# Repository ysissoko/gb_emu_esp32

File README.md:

# GB ESP32 Emulator

A Game Boy (DMG) and Game Boy Color (CGB) emulator running on the **ESP32-S3** microcontroller, built with ESP-IDF and FreeRTOS. The project includes a custom PCB design and achieves ~59.7 FPS with cycle-accurate emulation on embedded hardware.

---

## Features

### Emulation Core
- **Cycle-accurate SM83 CPU** — full base instruction set + CB-prefixed opcodes, correct flag behavior, HALT bug
- **Interrupt system** — VBLANK, STAT, TIMER, SERIAL, JOYPAD with proper IME/EI delay semantics
- **DMA** — OAM DMA (640 T-cycles), General DMA, and HDMA (HBlank-triggered 16-byte blocks)
- **Timer** — DIV, TIMA/TMA/TAC with falling-edge detection and 4-M-cycle overflow delay
- **Scanline PPU** — background, window, and sprite (up to 10/scanline) layers; STAT interrupts edge-triggered on LY/LYC comparison
- **Boot ROM** — 256-byte DMG boot ROM execution

### Game Boy Color (CGB)
- Mode detection via cartridge header byte `0x0143`
- VRAM banking (`VBK` 0xFF4F) — 2 × 8 KB banks in PSRAM
- WRAM banking (`SVBK` 0xFF70) — banks 2–7 in PSRAM
- CGB palette RAM — 8 BG + 8 OBJ palettes via `BGPI/BGPD`, `OBPI/OBPD`
- Tile attributes from VRAM bank 1 (palette index, H/V flip, VRAM bank select, BG-to-OBJ priority)
- 15-bit RGB color with GBC color correction (Gambatte-style formula)
- Double-speed CPU mode (`KEY1` 0xFF4D) — 2× CPU cycles, PPU/timer at 1×

### Cartridge Support (MBC)
| MBC | ROM Banks | RAM Banks | Notes |
|-----|-----------|-----------|-------|
| MBC1 | 32 | 4 | 512 KB ROM / 32 KB RAM |
| MBC2 | 16 | — | 512 × 4-bit internal RAM |
| MBC3 | 128 | 4 | + Real-Time Clock (RTC) |
| MBC5 | 512 | 16 | Most GBC games |

Extended ROM banks (>32 KB) are stored in PSRAM.

### Display
- **ST7789V** 240×240 SPI LCD at 80 MHz
- Game Boy 160×144 output upscaled to 240×240 (1.5×, centered)
- RGB565 framebuffer → BGR565 conversion for panel wiring
- Chunked DMA transfers (48-line chunks, 3 transfers per frame)
- Asynchronous rendering task — display I/O never blocks the emulation loop

### Storage & Saves
- SD card (FAT32, SPI-shared bus) for ROMs and save files
- `.sav` files for battery-backed SRAM, auto-saved every ~16 frames
- RTC persistence across sessions (MBC3)
- Async save task pinned to Core 0

### Input
- 8 tactile buttons — A, B, SELECT, START, UP, DOWN, LEFT, RIGHT
- Active-LOW GPIO with internal pull-ups and 20 ms debounce
- Joypad interrupt on key press

### Menu
- ROM browser with scrollable list (up to 64 entries)
- Text rendering on LCD, joypad navigation
- Menu framebuffer (~150 KB) freed before ROM loading

---

## Architecture

```
┌──────────────────────────────────────────────────────────────────┐
│                         Emulator                                 │
│              State machine: MENU ↔ RUNNING_GAME                  │
│         Task scheduling, ROM loading, component wiring           │
└───────────────────┬──────────────────────────────────────────────┘
                    │
       ┌────────────┼────────────┐
       │            │            │
┌──────▼──────┐ ┌───▼──────┐ ┌──▼──────────┐
│    CPU      │ │   PPU    │ │  MemoryBus  │
│  (SM83)     │ │ Scanline │ │   (MMU)     │
│  Executes   │ │ renderer │ │  Banking    │
│  instrs     │ │ 456 cy/  │ │  I/O mux   │
│  ~60 FPS    │ │ scanline │ │  MBC 1/3/5 │
└──────┬──────┘ └───┬──────┘ └──┬──────────┘
       │            │            │
       └────────────┼────────────┘
                    │
     ┌──────────────┼──────────────────┐
     │              │                  │
┌────▼───┐    ┌─────▼────┐    ┌───────▼────┐
│ Timer  │    │  Joypad  │    │  APU/Ser.  │
│DIV/TIMA│    │8 buttons │    │  (stub)    │
└────────┘    └──────────┘    └────────────┘

Display pipeline:
PPU framebuffer ──► Async render task ──► ST7789V (DMA, 3 chunks)

Storage:
SD card (FAT32) ──► ROM loading / .sav files ──► async save task
```

### Component Breakdown

| Component | File | Responsibility |
|-----------|------|----------------|
| Emulator | `emulator.cpp` | App states, task creation, ROM lifecycle |
| CPU | `cpu.cpp` (1 654 lines) | SM83 instruction execution, interrupts, DMA |
| PPU | `ppu.cpp` (754 lines) | Scanline rendering, STAT, VBLANK, CGB palettes |
| MemoryBus | `memory_bus.cpp` (1 143 lines) | Address decoding, MBC, PSRAM banking, I/O registers |
| Timer | `timer.cpp` | DIV/TIMA/TMA/TAC, overflow delay |
| Joypad | `joypad.hpp` | GPIO debounce, P14/P15 multiplexed reads |
| LCD Display | `lcd_display.cpp` | ST7789V SPI + DMA, RGB565 output |
| Storage | `storage.cpp` | SD card, FAT32, ROM enumeration |
| Save Manager | `save_manager.cpp` | SRAM persistence, async write to `.sav` |
| Menu | `menu.cpp` | ROM browser UI, framebuffer rendering |
| APU | `apu.cpp` | Stub — register map only |
| Serial | `serial.cpp` | Stub — SB/SC, debug accumulation |

---

## Memory Map

| Address | Region |
|---------|--------|
| `0x0000–0x00FF` | Boot ROM (DMG, 256 B; disabled after boot) |
| `0x0000–0x3FFF` | ROM Bank 0 (fixed) |
| `0x4000–0x7FFF` | ROM Bank N (MBC-switched, in PSRAM) |
| `0x8000–0x9FFF` | VRAM (8 KB; bank 0/1 in CGB via PSRAM) |
| `0xA000–0xBFFF` | External RAM (MBC; up to 32 KB in PSRAM) |
| `0xC000–0xCFFF` | WRAM Bank 0 |
| `0xD000–0xDFFF` | WRAM Bank 1 (banks 2–7 in CGB via PSRAM) |
| `0xE000–0xFDFF` | Echo RAM (mirrors 0xC000–0xDDFF) |
| `0xFE00–0xFE9F` | OAM (160 B, sprite attributes) |
| `0xFF00–0xFF7F` | I/O Registers |
| `0xFF80–0xFFFE` | HRAM (127 B) |
| `0xFFFF` | IE register |

---

## Hardware

### Microcontroller — ESP32-S3-WROOM-1
- Dual-core Xtensa LX7 at 240 MHz
- 512 KB internal SRAM + 8 MB PSRAM (extended ROM/RAM banks, CGB extras)
- 16 MB Flash

### Pin Mapping

| Function | GPIO |
|----------|------|
| **Joypad** | |
| A | 5 |
| B | 6 |
| UP | 15 |
| DOWN | 16 |
| RIGHT | 17 |
| LEFT | 18 |
| START | 21 |
| SELECT | 47 |
| **SPI Bus (shared)** | |
| MOSI | 11 |
| MISO | 13 |
| SCK | 12 |
| **ST7789V LCD** | |
| CS | 10 |
| RST | 8 |
| DC | 9 |
| Backlight | 7 |
| **SD Card** | |
| CS | 4 |
| **Battery ADC** | 38 |
| **Status LEDs** | 41, 42 |
| **USB** | 19 (D−), 20 (D+) |

### PCB
A custom KiCad board design is included in `main_board/` with JLCPCB production files. The board integrates the ESP32-S3, ST7789V LCD connector, SD slot, LiPo charging circuit, 8 tactile buttons, RGB LED, and USB-C port.

---

## Performance Optimizations

- **IRAM placement** (`IRAM_ATTR`) on all hot-path functions (CPU execute, PPU step, memory read/write) — avoids flash cache misses on the Xtensa core
- **Branch prediction hints** (`LIKELY` / `UNLIKELY` macros) throughout instruction dispatch
- **Async PPU rendering** — PPU queues completed framebuffers; a dedicated FreeRTOS task drives the LCD, so display I/O never stalls the emulation loop
- **Chunked DMA** — 48-line (23 KB) buffers sent in 3 transfers; DMA completion semaphore prevents tearing
- **Frame skipping** — dynamically skips PPU rendering when the CPU falls behind
- **Compiler flags** — `-O3 -ffast-math -funroll-loops` (see `CMakeLists.txt` / `optimize.sh`)
- **ScanlineContext** struct — caches frequently-read PPU registers for each scanline to avoid repeated MMU calls

---

## Build

### Prerequisites
- [ESP-IDF](https://docs.espressif.com/projects/esp-idf/en/latest/) v5.x
- ESP32-S3 target

### Steps

```bash
# Configure target
idf.py set-target esp32s3

# Build
idf.py build

# Flash and monitor
idf.py -p /dev/ttyUSB0 flash monitor
```

### SD Card Setup
Format the SD card as FAT32 and place ROM files (`.gb` / `.gbc`) in a `roms/` folder at the root.

---

## Project Structure

```
gb_esp32_emulator/
├── main/                  # Emulator source (~6 800 lines of C++)
│   ├── emulator.cpp/hpp   # Main controller
│   ├── cpu.cpp/hpp        # SM83 CPU
│   ├── ppu.cpp/hpp        # PPU / renderer
│   ├── memory_bus.cpp/hpp # MMU / MBC
│   ├── timer.cpp/hpp      # Timer
│   ├── joypad.hpp         # Input
│   ├── lcd_display.cpp/hpp# ST7789V driver
│   ├── storage.cpp/hpp    # SD card
│   ├── save_manager.cpp/hpp
│   ├── menu.cpp/hpp       # ROM browser UI
│   ├── apu.cpp/hpp        # Audio (stub)
│   ├── serial.cpp/hpp     # Serial (stub)
│   ├── gpio_pins.hpp      # Pin definitions
│   └── spi.hpp            # Shared SPI init
├── main_board/            # KiCad PCB design + JLCPCB files
├── docs/                  # Architecture notes, CGB refactor plan
├── pandocs_sources/       # Game Boy hardware reference
├── CMakeLists.txt
└── sdkconfig              # ESP-IDF build configuration
```

---

## Roadmap

- [ ] APU — 4-channel audio output
- [ ] Link cable / serial multiplayer
- [ ] CGB boot ROM
- [ ] Per-HBlank HDMA state machine
- [ ] Wi-Fi ROM loading via ESP32 network stack
- [ ] `dmg_acid2` / `cgb_acid2` test ROM validation

---

## References

- [Pan Docs](https://gbdev.io/pandocs/) — Game Boy hardware documentation
- [Game Boy CPU Manual](http://marc.rawer.de/Gameboy/Docs/GBCPUman.pdf)
- [Gambatte](https://github.com/sinamas/gambatte) — color correction formula
- [ESP-IDF Documentation](https://docs.espressif.com/projects/esp-idf/en/latest/)

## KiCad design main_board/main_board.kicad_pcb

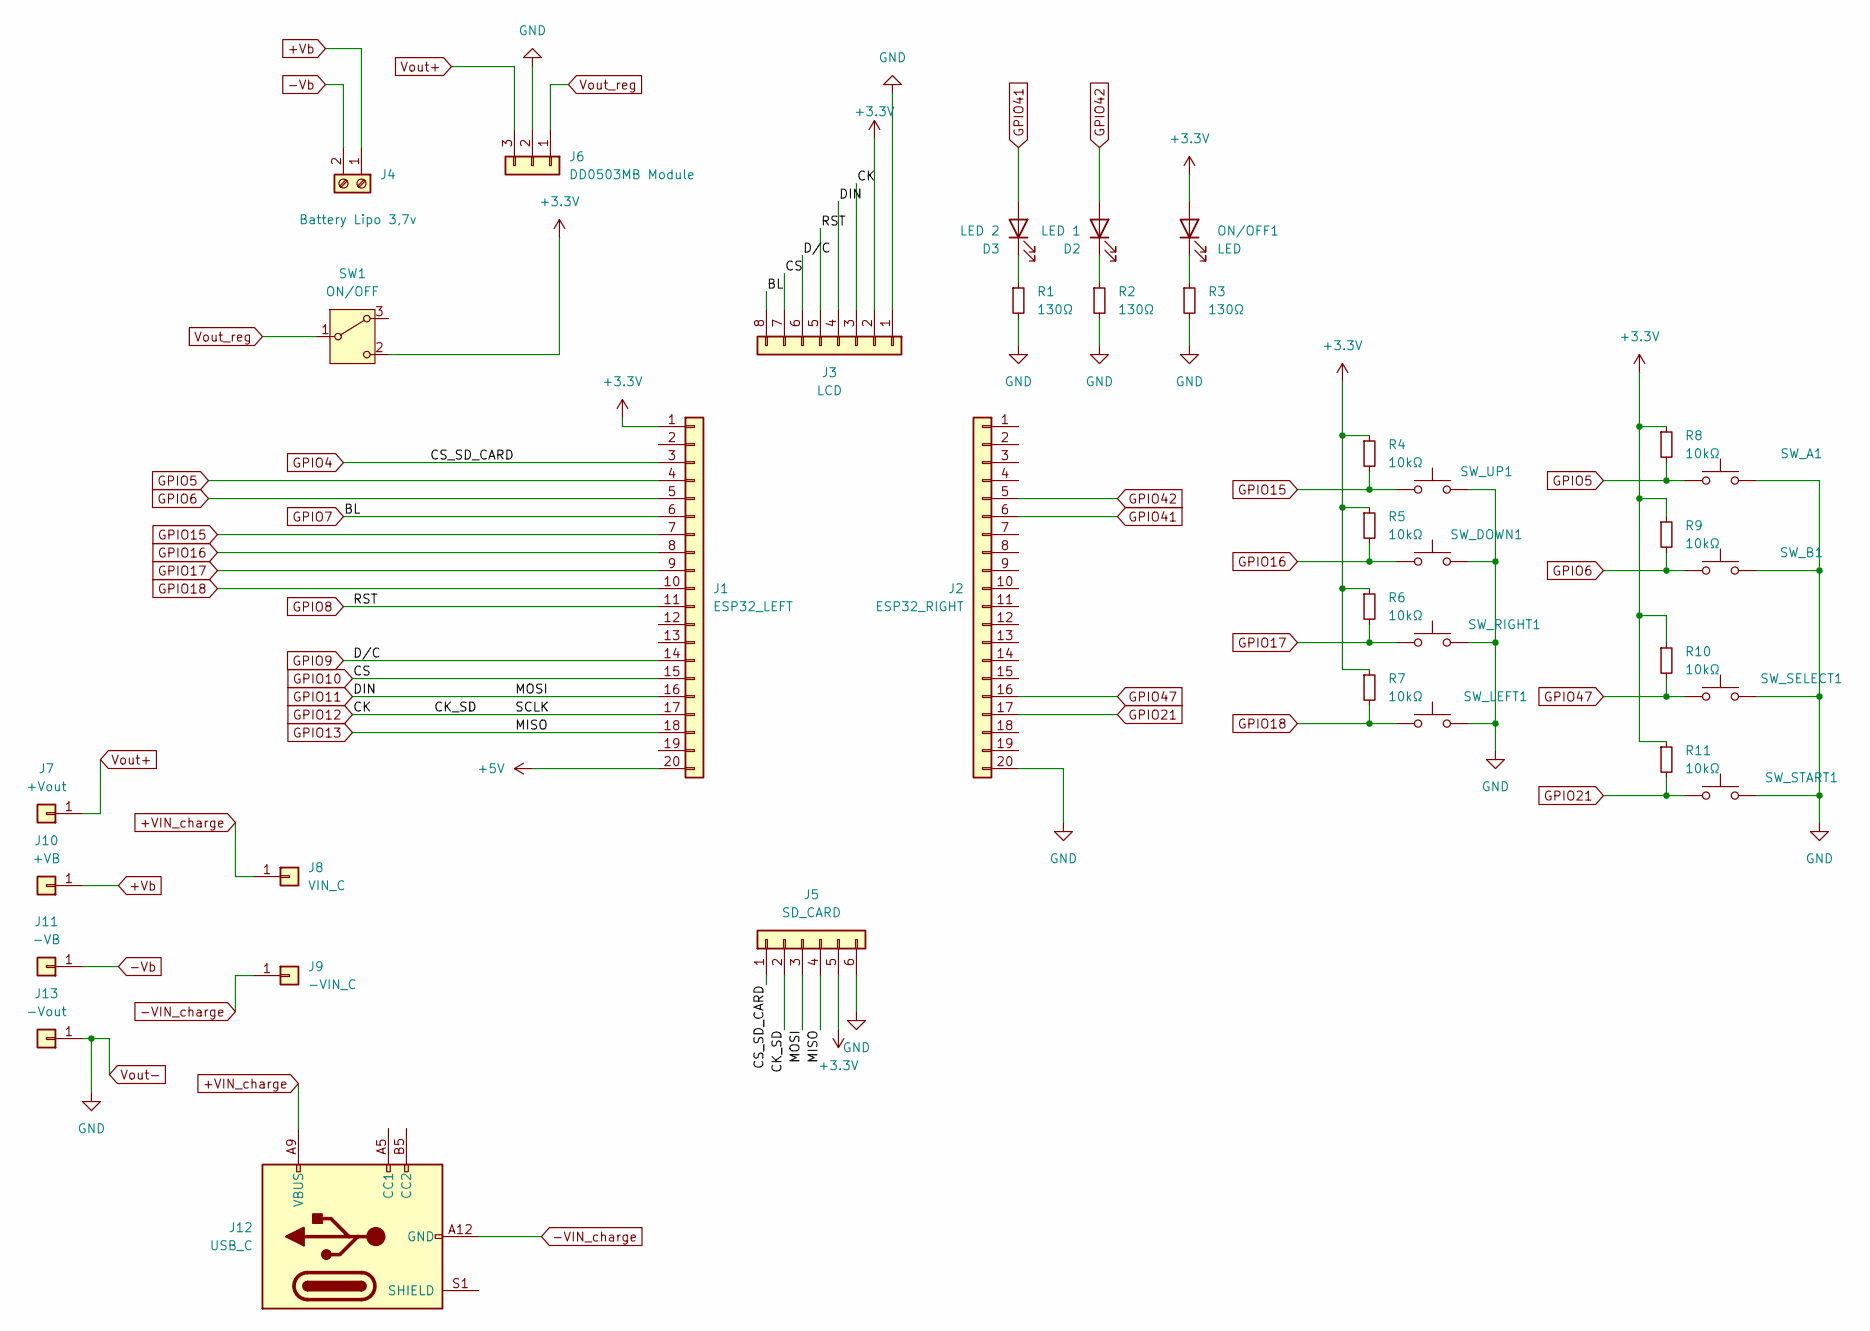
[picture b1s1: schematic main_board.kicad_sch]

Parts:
D2: LED 1; LED_1206_3216Metric
D3: LED 2; LED_1206_3216Metric
J1: ESP32_LEFT; PinSocket_1x20_P2.54mm_Vertical
J2: ESP32_RIGHT; PinSocket_1x20_P2.54mm_Vertical
J3: LCD; PinSocket_1x08_P2.54mm_Vertical
J4: Battery Lipo 3,7v; JST_EH_B2B-EH-A_1x02_P2.50mm_Vertical
J5: SD_CARD; PinSocket_1x06_P2.54mm_Vertical
J6: DD0503MB Module; PinSocket_1x03_P2.54mm_Vertical
J7: +Vout; PinHeader_1x01_P2.54mm_Vertical
J8: VIN_C; PinHeader_1x01_P2.54mm_Vertical
J9: -VIN_C; PinHeader_1x01_P2.54mm_Vertical
J10: +VB; PinHeader_1x01_P2.54mm_Vertical
J11: -VB; PinHeader_1x01_P2.54mm_Vertical
J12: USB_C; USB_C_Receptacle_GCT_USB4125-xx-x_6P_TopMnt_Horizontal
J13: -Vout; PinHeader_1x01_P2.54mm_Vertical
ON/OFF1: LED; LED_1206_3216Metric
R1, R2, R3: 130Ω; R_0805_2012Metric
R4, R5, R6, R7, R8, R9, R10, R11: 10kΩ; R_0805_2012Metric
SW1: ON/OFF; SW_Slide_SPDT_Angled_CK_OS102011MA1Q
SW_A1: SW_PUSH_6mm
SW_B1: SW_PUSH_6mm
SW_DOWN1: SW_PUSH_6mm
SW_LEFT1: SW_PUSH_6mm
SW_RIGHT1: SW_PUSH_6mm
SW_SELECT1: SW_Push; SW_PUSH_6mm
SW_START1: SW_Push; SW_PUSH_6mm
SW_UP1: SW_PUSH_6mm

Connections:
+3.3V: J1.1, J3.2, J5.5, ON/OFF1.2 (A), R4.1, R5.1, R6.1, R7.1, R8.1, R9.1, R10.1, R11.1, SW1.2 (C)
+5V: J1.20
+VIN_charge: J8.1, J12.A9 (VBUS), J12.B9 (VBUS)
+Vb: J4.1, J10.1
-VIN_charge: J9.1, J12.A12 (GND), J12.B12 (GND)
-Vb: J4.2, J11.1
GPIO4: J1.3, J5.1
GPIO5: J1.4, R8.2, SW_A1.1
GPIO6: J1.5, R9.2, SW_B1.1
GPIO7: J1.6, J3.8
GPIO8: J1.11, J3.5
GPIO9: J1.14, J3.6
GPIO10: J1.15, J3.7
GPIO11: J1.16, J3.4, J5.3
GPIO12: J1.17, J3.3, J5.2
GPIO13: J1.18, J5.4
GPIO15: J1.7, R4.2, SW_UP1.1
GPIO16: J1.8, R5.2, SW_DOWN1.1
GPIO17: J1.9, R6.2, SW_RIGHT1.1
GPIO18: J1.10, R7.2, SW_LEFT1.1
GPIO21: J2.17, R11.2, SW_START1.1
GPIO41: D3.2 (A), J2.6
GPIO42: D2.2 (A), J2.5
GPIO47: J2.16, R10.2, SW_SELECT1.1
unnamed: D2.1 (K), R2.1
unnamed: D3.1 (K), R1.1
unnamed: ON/OFF1.1 (K), R3.1
Vout+: J6.3, J7.1
Vout-: J2.20, J3.1, J5.6, J6.2, J13.1, R1.2, R2.2, R3.2, SW_A1.2, SW_B1.2, SW_DOWN1.2, SW_LEFT1.2, SW_RIGHT1.2, SW_SELECT1.2, SW_START1.2, SW_UP1.2
Vout_reg: J6.1, SW1.1 (B)

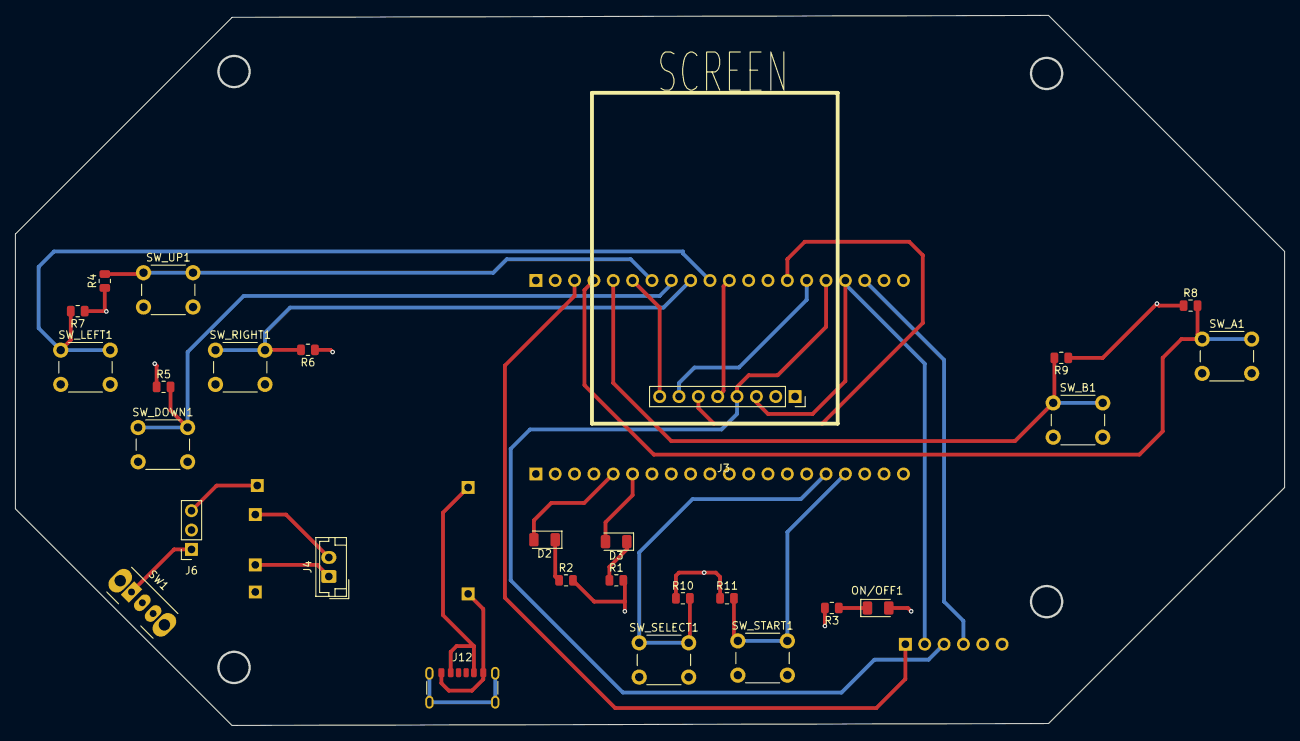
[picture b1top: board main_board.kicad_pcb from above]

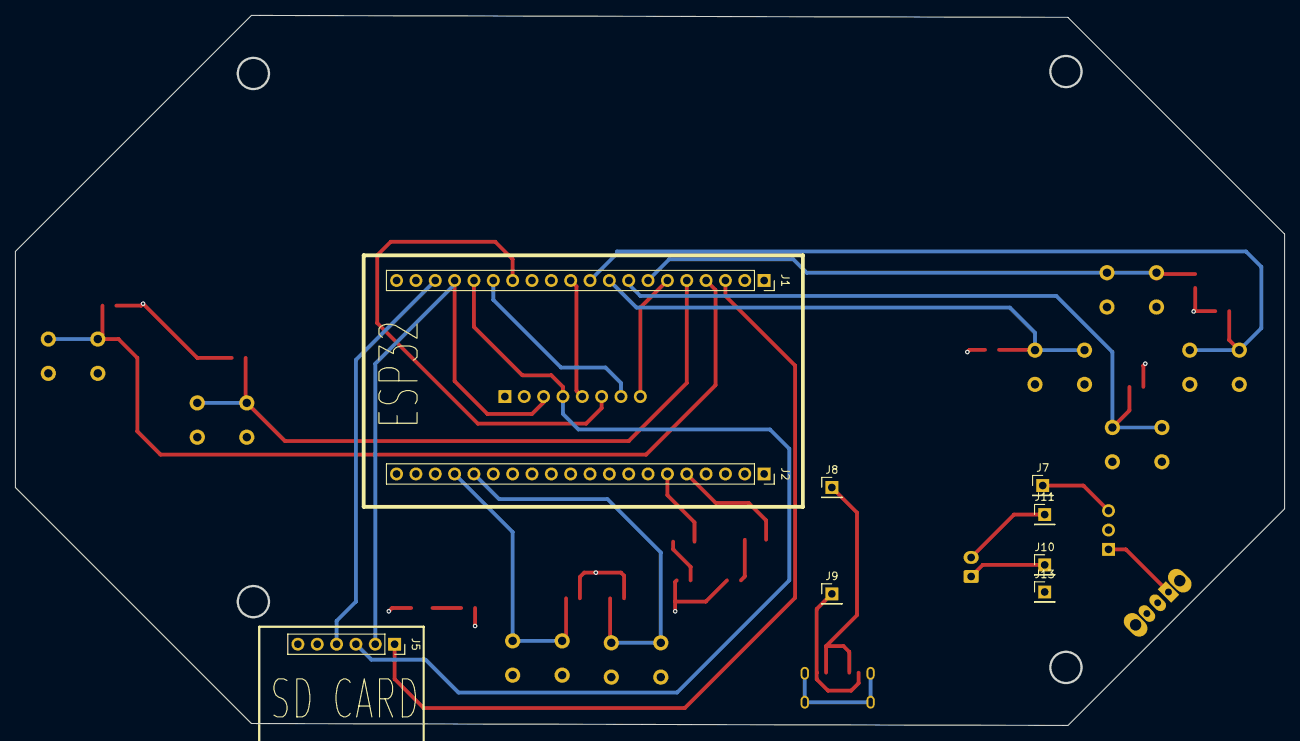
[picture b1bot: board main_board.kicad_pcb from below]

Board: 4 copper layers, 166.6 x 93.2 mm, 36 parts (9 on the bottom side), 29 nets.

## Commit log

2025-12-24 feat: op codes handling in cpu
2025-12-25 feat: add ppu implementation
2025-12-25 feature: display frame buffer on lcd display
2025-12-25 add debouncing for button pressed
2025-12-26 interrupt vblank, joypad and lcd stat implemented
2025-12-26 timer implementation
2025-12-26 add serial debugging capability
2025-12-26 fix link issues and define if_register as mutable to be able to modify it in const function
2025-12-26 feat: implement rom selection
2025-12-31 feat: sd card working
2025-12-31 feat: working emulator with performance issue
2026-01-01 feat: optimisations
2026-01-01 wip: emulator optimization
2026-01-02 added optimizations
2026-01-02 halt optimization like Peanut GB
2026-01-02 fix: bug in carry computed after flag modication and handle halt bug
2026-01-02 wario land working
2026-01-02 ignore .DS_STORE file
2026-01-04 update timer feature
2026-01-04 optimize timer for cycle accuracy
2026-01-05 chore: ignoring pandocs documentation files
2026-01-05 fix: timers bugs according to pandocs
2026-01-05 fix: lcd display colors
2026-01-05 modifying menu
2026-01-05 centering game display
2026-01-05 clear entire screen before game display
2026-01-05 fix: compilation issues
2026-01-05 add save feature to emulator
2026-01-05 fix: problème d'affichage menu + probleme de timing cpu. instr_timing ok
2026-01-06 fix latest version
2026-01-06 debugging the ppu
2026-01-06 markdown file to fix the ppu timing synchronization issue
2026-01-06 fix: ppu not working stat interrupt checking after state changes
2026-01-06 wip: bootrom fix
2026-01-07 fix pokemon rom support - add bit masking for mbc access
2026-01-07 dr mario and super mario land works now
2026-01-07 refactor gpio pins defines in one file
2026-01-09 add basic main board schematics
2026-01-10 cgb architecture documents
2026-01-13 update main board schematics USB C and 3,3v regulator
2026-01-21 update PCB -- finish routing pcb
2026-02-04 Version 1 PCB finished
2026-02-04 pcb version 2 PCB mode
2026-02-06 chore: modify screen width & height
2026-02-09 change LCD , correct charger board footprint and PSP mode
2026-02-24 fix: scroll last frame duplication
2026-02-24 fix: lower spi frequency and fix incorrect bit shifting
2026-02-25 cgb mode sprite rendering handling in ppu
2026-02-25 feat: implement CGB mode support with VRAM and WRAM management
2026-02-25 feat: implement CGB mode CPU initialization and double-speed handling
2026-02-25 feat: link CGB resources to PPU and re-initialize CPU for CGB mode
2026-02-25 c++ developper agent added
2026-02-25 updating documentation
2026-02-25 updating cgb mode support checklist
2026-02-25 feat: enhance CGB mode support with HDMA and CPU stall handling
2026-02-25 feat: enhance MBC handling for MBC1 and MBC3 bank selection
2026-02-26 feat: enhance MBC5 support with extended ROM storage and bank selection logic
2026-02-26 feat: add GitHub Copilot instructions for GB/GBC ESP32 Emulator
2026-02-26 modifying the rgb color rendering for cgb
2026-02-28 feat: implement CPU instruction tracing and optimize palette handling for CGB mode
2026-02-28 fix: correct DMA cycle calculations and enhance PPU STAT register handling
2026-04-02 remap the pins to fit with the board
2026-04-03 scaling the display and handle palette for DMG rom display
2026-05-11 Add Readme file
2026-05-13 fix: mbc5 bank0 mapping
2026-05-13 fix: cpu speed handling
2026-05-13 fix: clear stat interrupt bit in ly register
2026-05-13 fix apu bugs for games that are waiting for the apu state
